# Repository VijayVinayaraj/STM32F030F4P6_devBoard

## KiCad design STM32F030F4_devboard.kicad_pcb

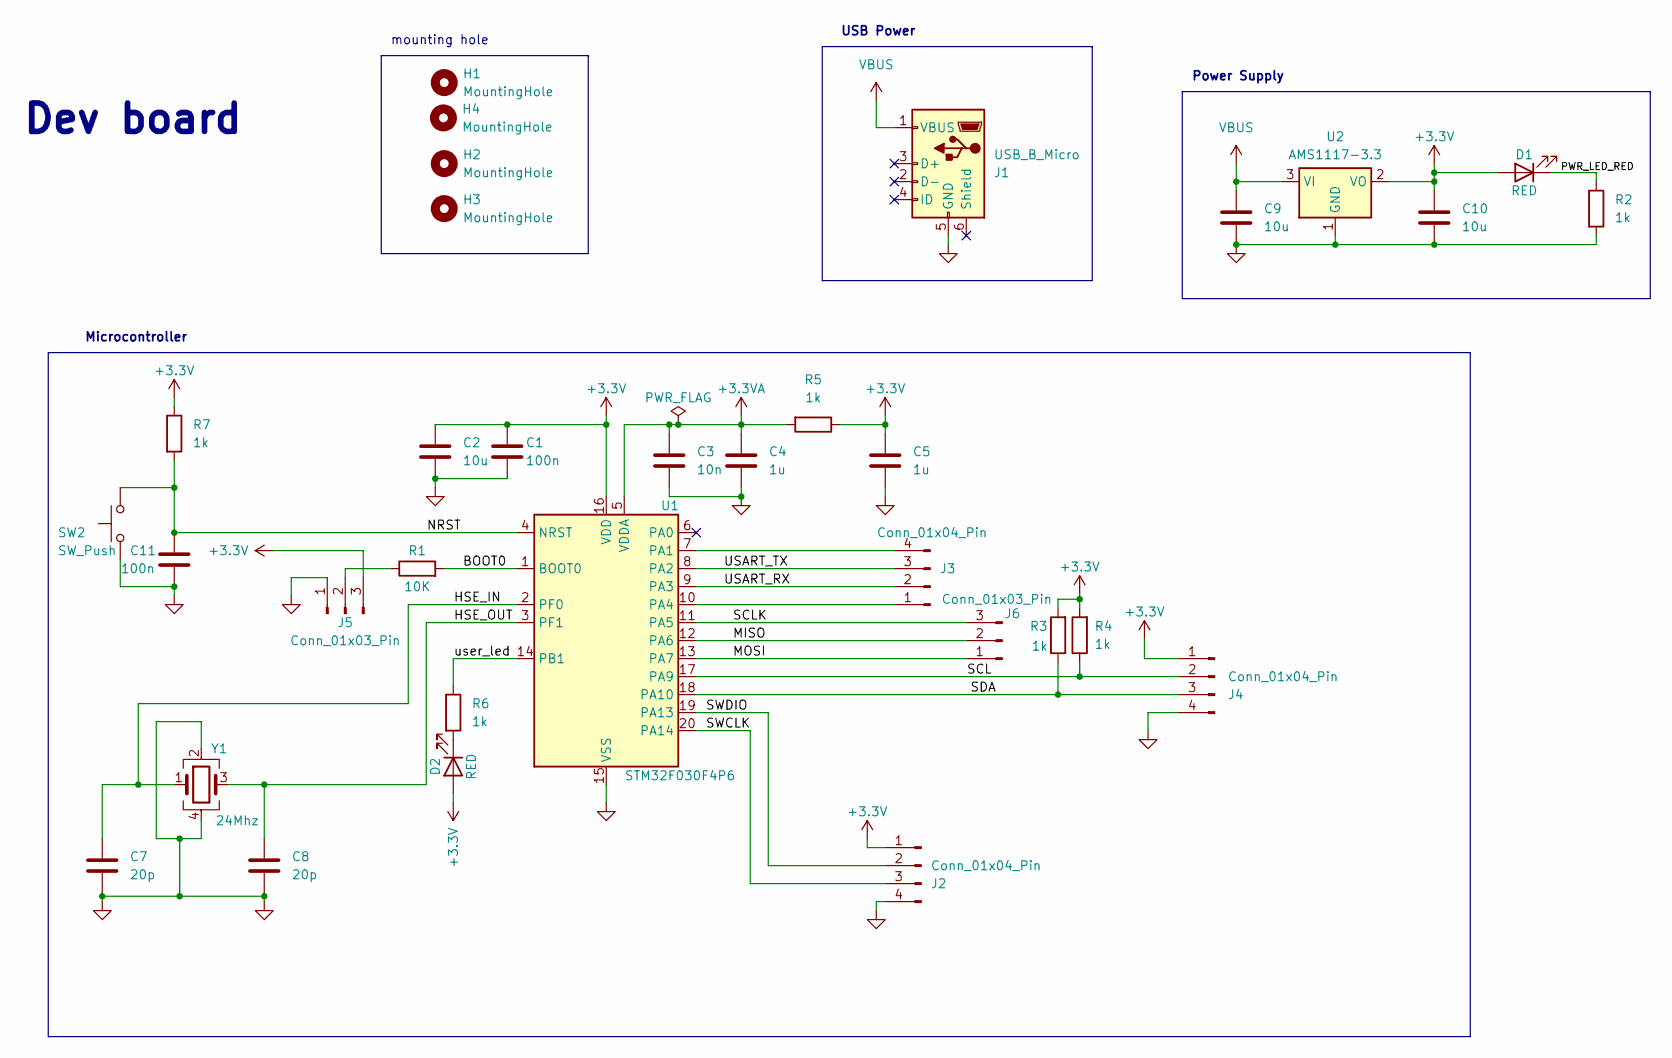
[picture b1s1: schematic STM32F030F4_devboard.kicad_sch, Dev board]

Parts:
C1, C11: 100n; C_0805_2012Metric
C2, C9, C10: 10u; C_0603_1608Metric
C3: 10n; C_0603_1608Metric
C4, C5: 1u; C_0603_1608Metric
C7, C8: 20p; C_0603_1608Metric
D1, D2: RED; LED_0603_1608Metric
H1, H2, H3, H4: MountingHole; MountingHole_2.2mm_M2
J1: USB_B_Micro; USB_Micro-B_Wuerth_629105150521
J2, J3, J4: Conn_01x04_Pin; PinHeader_1x04_P2.54mm_Vertical
J5, J6: Conn_01x03_Pin; PinHeader_1x03_P2.54mm_Vertical
R1: 10K; R_0603_1608Metric
R2, R3, R4, R5, R6, R7: 1k; R_0603_1608Metric
SW2: SW_Push; SW_SPST_PTS645
U1: STM32F030F4P6; TSSOP-20_4.4x6.5mm_P0.65mm
U2: AMS1117-3.3; SOT-223-3_TabPin2
Y1: 24Mhz; Crystal_SMD_3225-4Pin_3.2x2.5mm

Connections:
+3.3V: C1.1, C2.1, C5.1, C10.1, D1.2 (A), D2.2 (A), J2.1, J4.1, J5.3, R3.2, R4.2, R5.1, R7.1, U1.16 (VDD), U2.2 (VO)
+3.3VA: C3.1, C4.1, R5.2, U1.5 (VDDA)
/BOOT0: R1.2, U1.1 (BOOT0)
/HSE_IN: C7.1, U1.2 (PF0), Y1.1
/HSE_OUT: C8.1, U1.3 (PF1), Y1.3
/MISO: J6.2, U1.12 (PA6)
/MOSI: J6.1, U1.13 (PA7)
/NRST: C11.1, R7.2, SW2.2, U1.4 (NRST)
/PWR_LED_RED: D1.1 (K), R2.1
/SCL: J4.2, R4.1, U1.17 (PA9)
/SCLK: J6.3, U1.11 (PA5)
/SDA: J4.3, R3.1, U1.18 (PA10)
/SWCLK: J2.3, U1.20 (PA14)
/SWDIO: J2.2, U1.19 (PA13)
/USART_RX: J3.2, U1.9 (PA3)
/USART_TX: J3.3, U1.8 (PA2)
/user_led: R6.1, U1.14 (PB1)
GND: C1.2, C2.2, C3.2, C4.2, C5.2, C7.2, C8.2, C9.2, C10.2, C11.2, J1.5 (GND), J2.4, J4.4, J5.1, R2.2, SW2.1, U1.15 (VSS), U2.1 (GND), Y1.2, Y1.4
unnamed: D2.1 (K), R6.2
unnamed: J3.1, U1.10 (PA4)
unnamed: J3.4, U1.7 (PA1)
unnamed: J5.2, R1.1
VBUS: C9.1, J1.1 (VBUS), U2.3 (VI)

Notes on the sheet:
USB Power
mounting hole
Power Supply
Microcontroller
Dev board

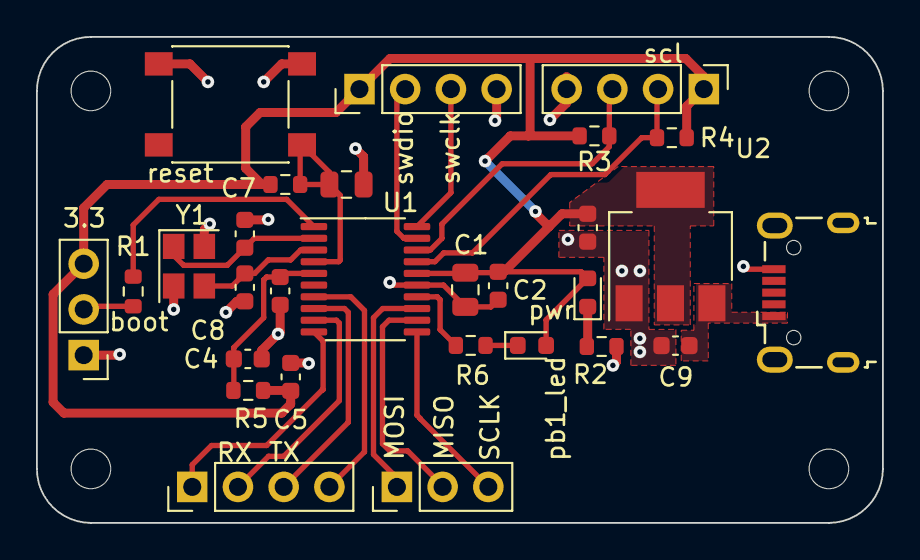
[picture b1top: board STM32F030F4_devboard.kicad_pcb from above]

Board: 2 copper layers, 47.0 x 27.0 mm, 33 parts (0 on the bottom side), 23 nets.

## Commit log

2024-03-02 finish schematic
2024-03-03 finish pcb routing
